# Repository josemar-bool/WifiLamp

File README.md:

# WifiLamp
Projeto de um interruptor wifi para lâmpada.

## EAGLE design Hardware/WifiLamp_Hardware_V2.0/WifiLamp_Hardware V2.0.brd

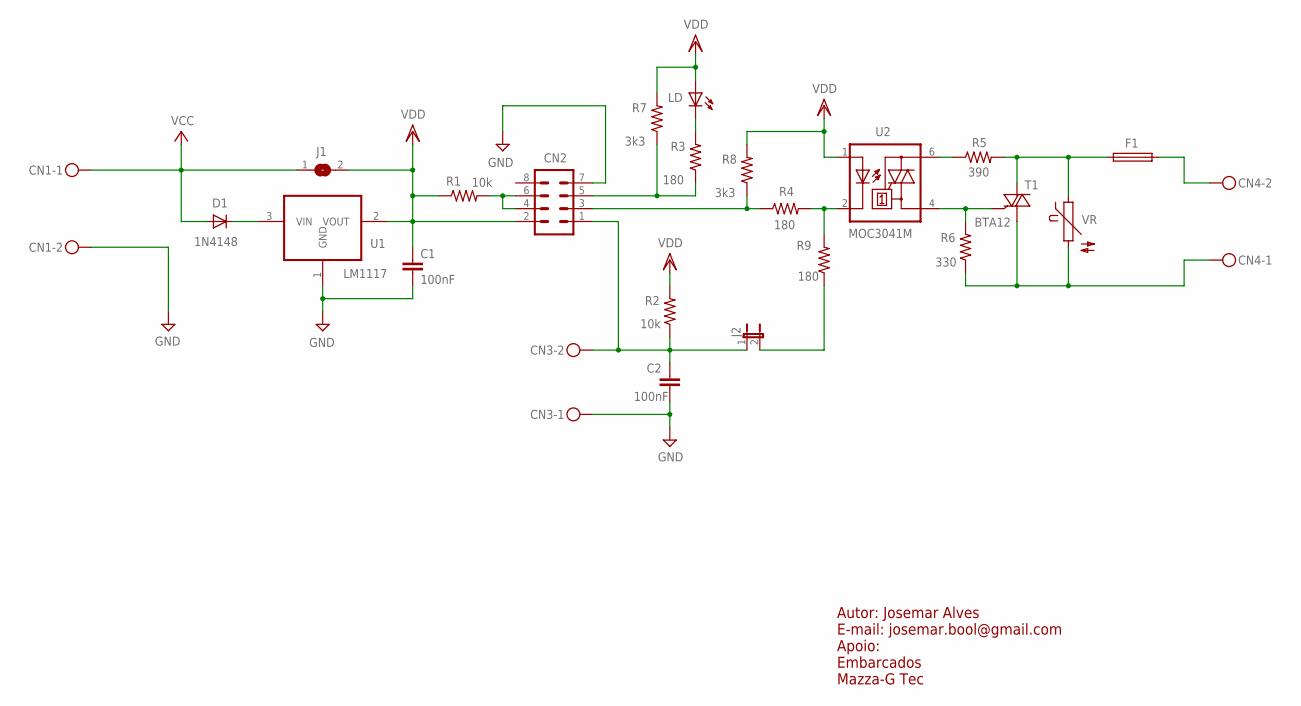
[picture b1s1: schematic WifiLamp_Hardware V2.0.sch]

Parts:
C1, C2: 100nF; C0805K
CN1, CN3, CN4: MKDSN1,5/2-5,08
CN2: MA04-2
D1: 1N4148; D-7.5
F1: FUSETR5; TR5
J1: SJ
J2: JP1E; JP1
LD: LED3MM
R1, R2: 10k; 0309V
R3, R4, R9: 180; 0309V
R5: 390; 0309V
R6: 330; 0309V
R7, R8: 3k3; 0309V
T1: BTA12; TO220BV
U1: LM1117; SOT223
U2: MOC3041M; DIL06
VR: S07K230

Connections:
FS: F1.1, R5.2, T1.T2 (A2), VR.1
unnamed: R5.1, U2.6 (A2)
unnamed: R6.2, T1.G, U2.4 (A1)
unnamed: R4.2, R9.2, U2.2 (C)
unnamed: CN2.3, R4.1, R8.1
unnamed: J2.2, R9.1
unnamed: CN4.2, F1.2
unnamed: D1.C, U1.3 (VIN)
unnamed: CN2.5, R3.1, R7.1
unnamed: C2.1, CN2.1, CN3.2, J2.1, R2.1
unnamed: LD.K (C), R3.2
unnamed: C1.1, CN2.2, J1.2, LD.A, R1.1, R2.2, R7.2, R8.2, U1.2 (VOUT), U2.1 (A)
unnamed: C1.2, C2.2, CN1.2, CN2.7, CN3.1, U1.1 (GND)
unnamed: CN2.4, CN2.6, R1.2
unnamed: CN1.1, D1.A, J1.1
unnamed: CN4.1, R6.1, T1.T1 (A1), VR.2

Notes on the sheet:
Autor: Josemar Alves E-mail: josemar.bool@gmail.com Apoio: Embarcados Mazza-G Tec

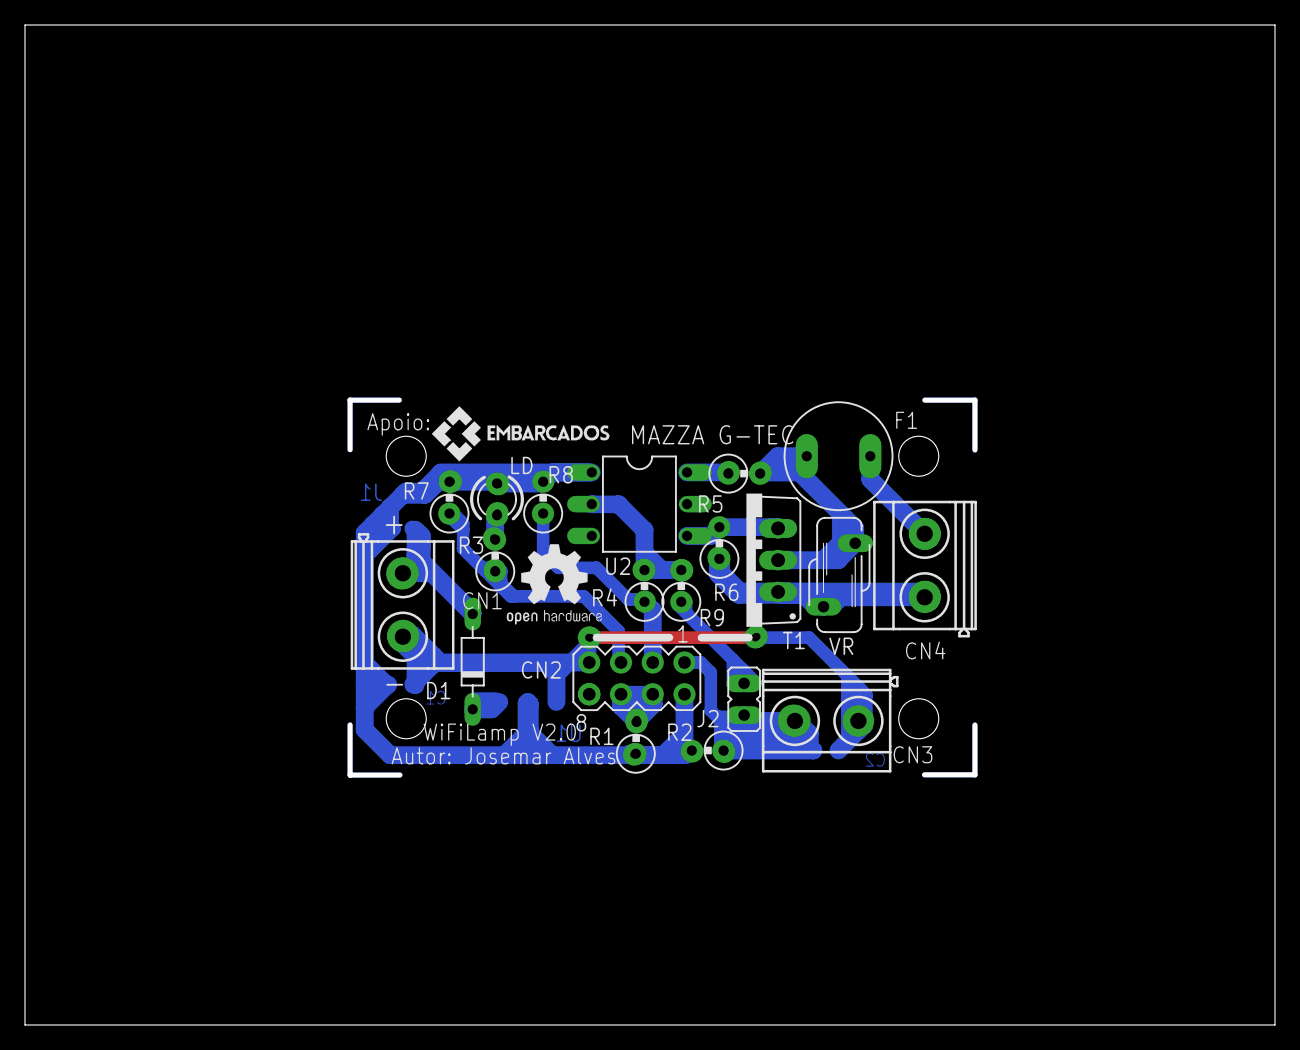
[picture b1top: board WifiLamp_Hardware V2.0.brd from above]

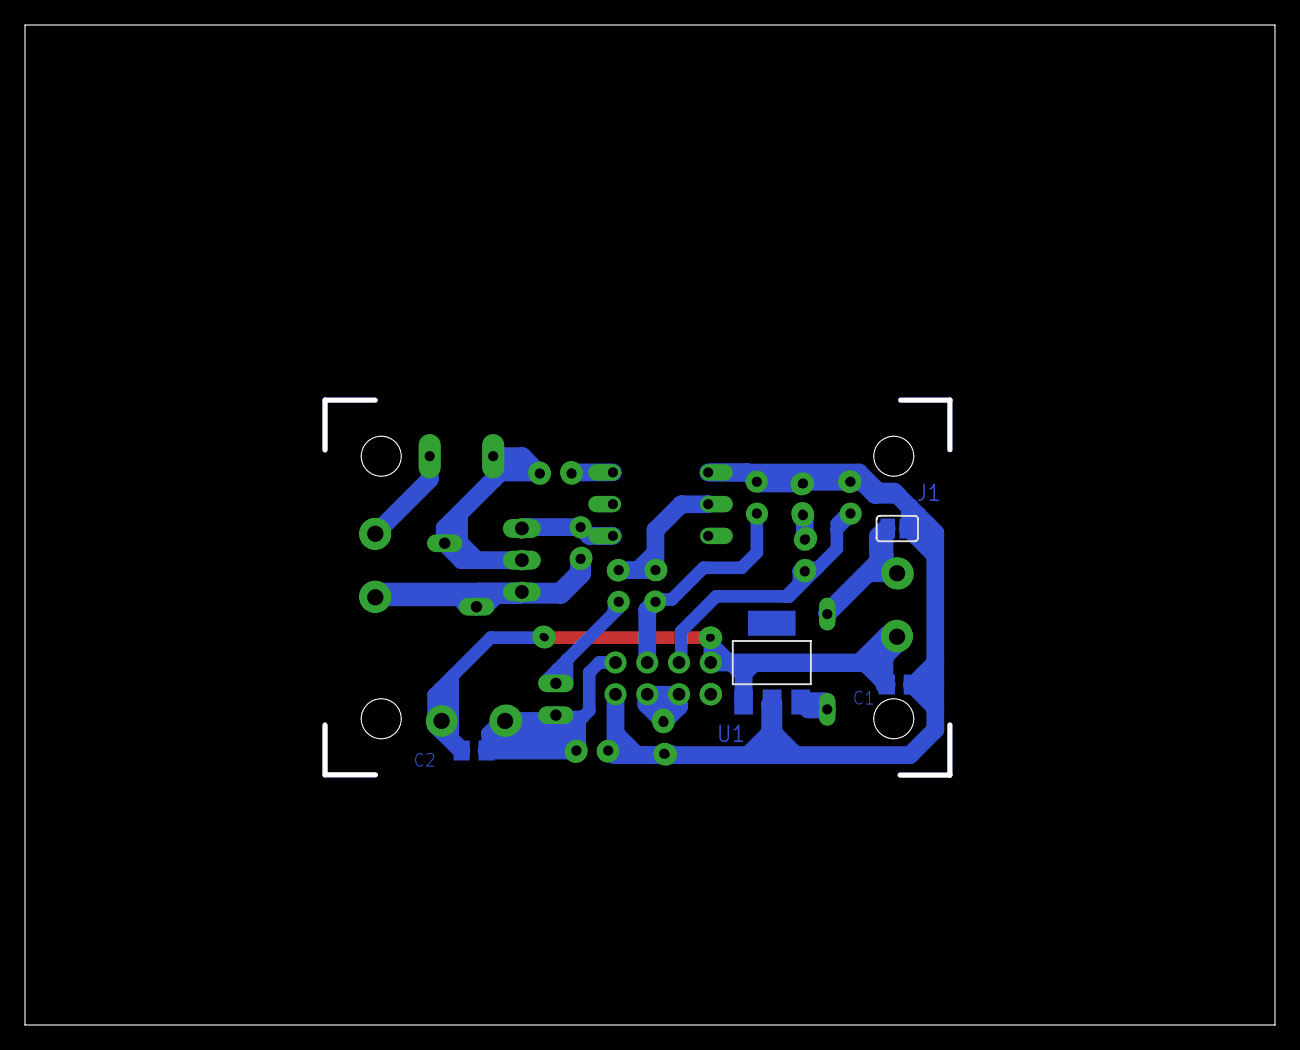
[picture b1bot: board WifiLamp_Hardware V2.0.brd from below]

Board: 2 copper layers, 99.6 x 79.6 mm, 24 parts (4 on the bottom side), 16 nets.

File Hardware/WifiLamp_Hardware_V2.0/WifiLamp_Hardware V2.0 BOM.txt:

Partlist exported from /home/josemar/Dropbox/Pisco IDC/Projeto WifiLamp/espelhoGit/WifiLamp/WifiLamp_Hardware_V2.0/WifiLamp_Hardware V2.0.sch at 14/11/16 16:11

Part Value           Device          Package         Description                                                                
C1   100nF           C-EUC0805K      C0805K          CAPACITOR, European symbol                                                 
C2   100nF           C-EUC0805K      C0805K          CAPACITOR, European symbol                                                 
CN1  MKDSN1,5/2-5,08 MKDSN1,5/2-5,08 MKDSN1,5/2-5,08 MKDSN 1,5/ 2-5,08 Printklemme                                              
CN2                  MA04-2          MA04-2          PIN HEADER                                                                 
CN3  MKDSN1,5/2-5,08 MKDSN1,5/2-5,08 MKDSN1,5/2-5,08 MKDSN 1,5/ 2-5,08 Printklemme                                              
CN4  MKDSN1,5/2-5,08 MKDSN1,5/2-5,08 MKDSN1,5/2-5,08 MKDSN 1,5/ 2-5,08 Printklemme                                              
D1   1N4148          DIODE-D-7.5     D-7.5           DIODE                                                                      
F1   FUSETR5         FUSETR5         TR5             Fuse                                                                       
J1                   SJ              SJ              SMD solder JUMPER                                                          
J2                   JP1E            JP1             JUMPER                                                                     
LD                   LED3MM          LED3MM          LED                                                                        
R1   10k             R-US_0309/V     0309V           RESISTOR, American symbol                                                  
R2   10k             R-US_0309/V     0309V           RESISTOR, American symbol                                                  
R3   180             R-US_0309/V     0309V           RESISTOR, American symbol                                                  
R4   180             R-US_0309/V     0309V           RESISTOR, American symbol                                                  
R5   390             R-US_0309/V     0309V           RESISTOR, American symbol                                                  
R6   330             R-US_0309/V     0309V           RESISTOR, American symbol                                                  
R7   3k3             R-US_0309/V     0309V           RESISTOR, American symbol                                                  
R8   3k3             R-US_0309/V     0309V           RESISTOR, American symbol                                                  
R9   180             R-US_0309/V     0309V           RESISTOR, American symbol                                                  
T1   BTA12           BT138-V         TO220BV         TRIAC                                                                      
U1   LM1117          REG1117         SOT223          800mA and 1A Low Dropout (LDO) Positive Regulator                          
U2   MOC3041M        MOC3041M        DIL06           6-Pin DIP Zero-Cross Optoisolators Triac Driver Output (250/400 Volt Peak) 
VR   S07K230         S07K230         S07K230         VARISTOR

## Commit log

2016-09-13 Progeto WifiLamp - Hardware V1.0
2016-11-14 Incluindo a versão 2.0 do hardware
2016-11-14 Removendo arquivos antigos
2016-11-14 Incluido arquivos gerber e BOM
2017-02-02 Inclusao do firmware e app
2017-02-02 Inclusão dos gerbers e BOM do hardware V2
